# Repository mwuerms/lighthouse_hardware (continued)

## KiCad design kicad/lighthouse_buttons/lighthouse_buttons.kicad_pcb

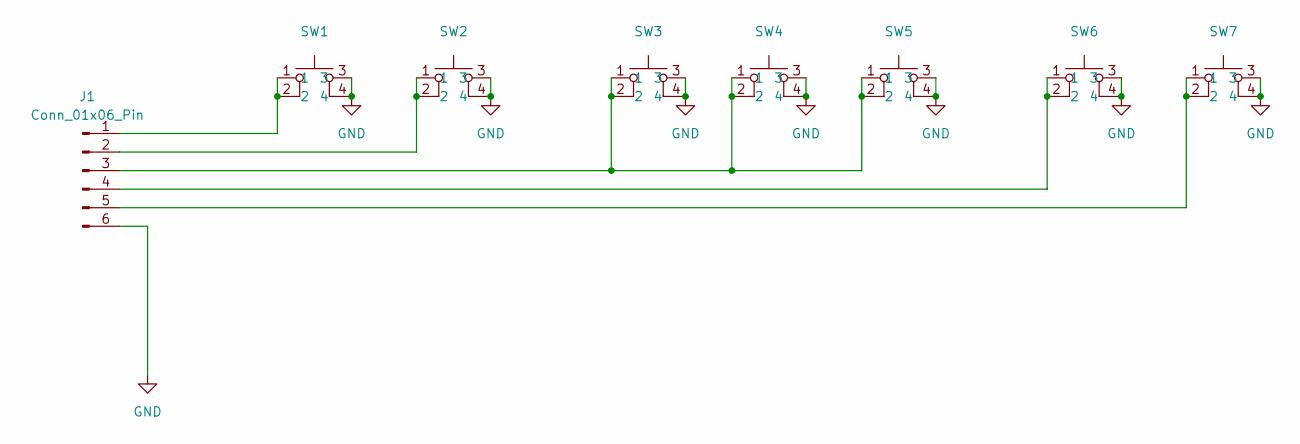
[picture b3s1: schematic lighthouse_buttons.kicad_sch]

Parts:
J1: Conn_01x06_Pin; con_1x6_1.27mm_long_pads
SW1, SW2, SW3, SW4, SW5, SW6, SW7: PTS526

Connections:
GND: J1.6, SW1.3, SW1.4, SW2.3, SW2.4, SW3.3, SW3.4, SW4.3, SW4.4, SW5.3, SW5.4, SW6.3, SW6.4, SW7.3, SW7.4
unnamed: J1.1, SW1.1, SW1.2
unnamed: J1.2, SW2.1, SW2.2
unnamed: J1.3, SW3.1, SW3.2, SW4.1, SW4.2, SW5.1, SW5.2
unnamed: J1.4, SW6.1, SW6.2
unnamed: J1.5, SW7.1, SW7.2

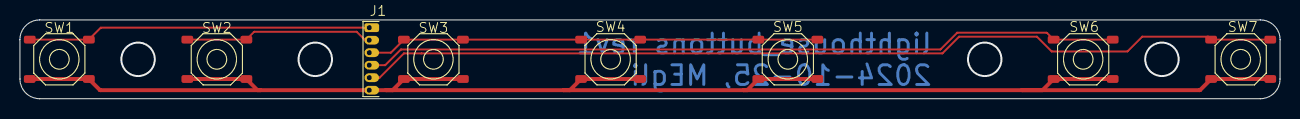
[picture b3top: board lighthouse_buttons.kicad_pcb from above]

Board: 2 copper layers, 128.0 x 8.0 mm, 8 parts (0 on the bottom side), 6 nets.

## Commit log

2024-05-15 added readme + started buoy model
2024-05-15 1st version of buoy case done, try it out
2024-05-15 added buoy schematics, not 100 % done yet
2024-05-15 update schematics
2024-05-15 added more sensors
2024-05-15 added cad display test
2024-05-23 add display
2024-05-23 added 2nd version of display covers
2024-05-23 started with case for lighthouse
2024-05-25 added 60° side
2024-05-25 renamed file displayparts.scad to hexagonparts.scad
    also put led parts into ledparts.scad
2024-05-25 started putting front together
2024-05-26 simpler version of the side parts created
2024-05-28 bottom plate + buttons
2024-05-29 defined pcbs and buttons
    and separated parts into files according to its function
2024-05-29 added edge stiffener 60°
2024-05-30 added PLFA-M3-1 press fit inserts to mount side panels
    also added mounting sides
    also added base pcb
2024-05-30 all mounts added and placed
2024-06-01 almost every part 3d designed, move to pcbs now
2024-06-02 export created 3d parts
2024-06-02 added center marking to led spacer
2024-06-02 started display pcb
2024-06-02 added lib
2024-06-03 white LED driver TPS61176RTER added in lib and sch
2024-06-06 much ado about LEDs :-)
2024-06-12 sch: all leds connected, also set all footprints
2024-06-19 started lighthouse base pcb
2024-09-20 added some ideas
2024-09-25 hw display placed red and white leds
2024-10-07 places both led drivers, started routing
2024-10-09 red leds routing, not done yet
2024-10-10 use 7*6 white LEDs in a row now, almost all leds connected
2024-10-10 100% routed
2024-10-27 started with button pcb
2024-10-27 rev1
2024-10-27 hardware for lighthouse display rev1 and button rev1 done
2024-10-30 added sheets for mcu and peripherials
2024-10-30 added FPPlayer and BC805M BLE Module
2024-10-30 schema v1 done
2024-11-02 schematics done
2024-11-02 started with pcb lighthouse_base
2024-11-06 lighthouse base rev 1 done
2025-09-28 mv files from rev0 to rev0/
2025-09-28 rev1: added 32 kHz XTAL, interrupt signals for VBUS + +5V, ... many more
2025-10-01 clean up libs
2025-10-01 display rev0, moved files
2025-10-01 removed lib
2025-10-01 renamed libs + added opt3004 to lib
2025-10-01 ordererd lighthouse display
2025-10-02 rev1 of base + display
